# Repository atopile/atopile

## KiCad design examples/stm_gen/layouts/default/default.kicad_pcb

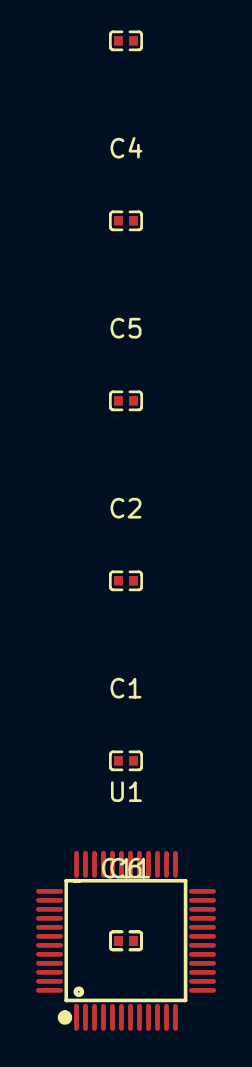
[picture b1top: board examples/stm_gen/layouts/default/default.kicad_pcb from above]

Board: 2 copper layers, 8 parts (0 on the bottom side), 3 nets, no tracks yet.

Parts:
C1, C2, C3, C4, C5, C6, C11: 0F; C0402
U1: LQFP-48_L7.0-W7.0-P0.50-LS9.0-BL

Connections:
hv: C1.1, C2.1, C3.1, C4.1, C5.1, C6.1, U1.9, U1.24, U1.36, U1.48
lv: C1.2, C2.2, C3.2, C4.2, C5.2, C6.2, C11.2, U1.8, U1.23, U1.35, U1.47
vbat-hv: C11.1, U1.1

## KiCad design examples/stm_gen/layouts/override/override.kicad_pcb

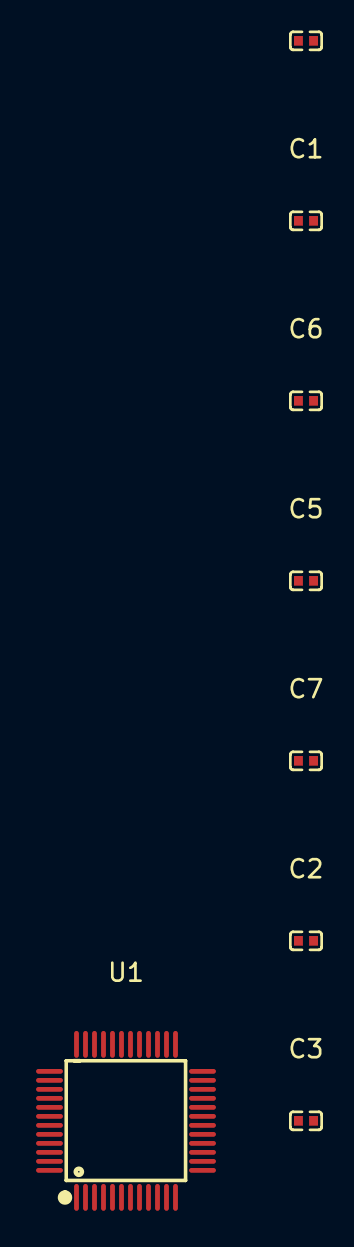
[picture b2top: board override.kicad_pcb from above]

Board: 2 copper layers, 8 parts (0 on the bottom side), 3 nets, no tracks yet.

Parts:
C1, C2, C3, C4, C5, C6, C7: 0F; C0402
U1: LQFP-48_L7.0-W7.0-P0.50-LS9.0-BL

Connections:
hv: C1.1, C2.1, C3.1, C4.1, C5.1, C6.1, U1.9, U1.24, U1.36, U1.48
lv: C1.2, C2.2, C3.2, C4.2, C5.2, C6.2, C7.2, U1.8, U1.23, U1.35, U1.47
vbat-hv: C7.1, U1.1

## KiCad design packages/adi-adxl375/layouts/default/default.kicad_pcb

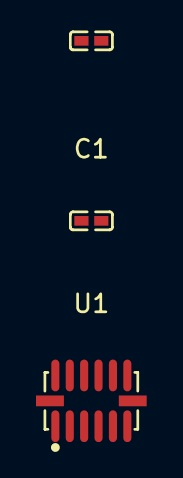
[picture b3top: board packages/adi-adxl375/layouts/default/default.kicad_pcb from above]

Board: 2 copper layers, 3 parts (0 on the bottom side), 4 nets, no tracks yet.

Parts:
C1, C2: 100nF ±10% 16V X7R; C0402
U1: LGA-14_L5.0-W3.0-P0.80-BL

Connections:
RESERVED: U1.3, U1.11
VDDI_O: C1.1, U1.1
VS: C2.1, U1.6
gnd: C1.2, C2.2, U1.2, U1.4, U1.5

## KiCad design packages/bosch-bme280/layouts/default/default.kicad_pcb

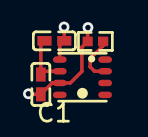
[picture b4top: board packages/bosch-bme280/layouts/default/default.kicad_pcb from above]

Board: 2 copper layers, 4 parts (0 on the bottom side), 4 nets.

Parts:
C1, C2: 100nF ±10% 16V X7R; C0402
R1: 10kΩ ±1% 62.5mW; R0402
U1: LGA-8_BME280_BL

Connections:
CSB: R1.2, U1.2
VDD: C1.1, U1.8
VDDIO: C2.1, R1.1, U1.6
gnd: C1.2, C2.2, U1.1, U1.7

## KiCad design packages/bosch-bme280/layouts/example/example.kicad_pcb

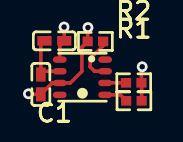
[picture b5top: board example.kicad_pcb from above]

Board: 2 copper layers, 6 parts (0 on the bottom side), 5 nets.

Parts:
C1, C2: 100nF ±10% 16V X7R; C0402
R1, R2, R3: 10kΩ ±1% 62.5mW; R0402
U1: LGA-8_BME280_BL

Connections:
CSB: R3.2, U1.2
SCK: R1.1, U1.4
SDI: R2.1, U1.3
gnd: C1.2, C2.2, U1.1, U1.7
hv: C1.1, C2.1, R1.2, R2.2, R3.1, U1.6, U1.8

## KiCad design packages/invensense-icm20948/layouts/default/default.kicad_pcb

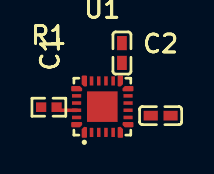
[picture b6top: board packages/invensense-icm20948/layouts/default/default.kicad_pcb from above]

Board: 2 copper layers, 4 parts (0 on the bottom side), 5 nets.

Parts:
C1, C2: 100nF ±10% 16V X7R; C0402
R1: 10kΩ ±1% 62.5mW; R0402
U1: QFN-24_L3.0-W3.0-P0.40-BL-EP

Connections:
RESV: U1.19, U1.20
VDD: C1.1, U1.13
VDDIO: C2.1, R1.1, U1.8
gnd: C1.2, C2.2, U1.18
nCS: R1.2, U1.22
